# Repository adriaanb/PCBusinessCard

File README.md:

# PCBusinessCard
Another PCB Business Card, this time combining the functionality of an Arduino Leonardo with a capacitive touch interface.

The aim is to provide new contacts some insights into my passions, way of working, and creative style. It also allows me to hand out a tool I use frequently and enable people to discover its potential..

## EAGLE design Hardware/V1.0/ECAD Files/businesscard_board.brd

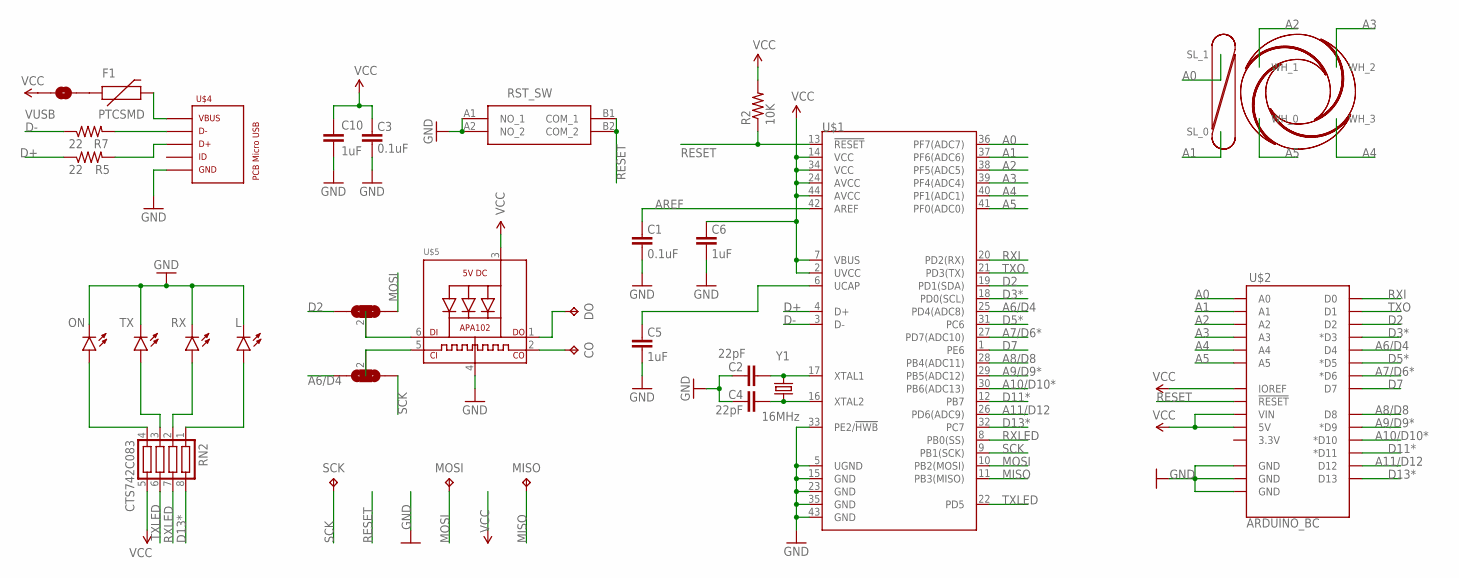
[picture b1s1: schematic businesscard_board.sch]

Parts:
C1, C3: 0.1uF; 0603-CAP
C2, C4: 22pF; 0603-CAP
C5, C6, C10: 1uF; 0603-CAP
CO: TPTP12R; TP12R
D2-/-°-MOSI, D4-/-°-SCK: SOLDER_JP_3WAY
DO: TPTP12R; TP12R
F1: PTCSMD; PTC-1206
L: LED; LED-0603_NOMARKER
MISO: TPTP12R; TP12R
MOSI: TPTP12R; TP12R
ON: LED; LED-0603_NOMARKER
R2: 10K; 0603-RES
R5, R7: 22; 0603-RES
RN2: CTS742C083
RST_SW: EVP-BB0AAB000; EVPBB0AAB000
RX: LED; LED-0603_NOMARKER
SCK: TPTP12R; TP12R
TX: LED; LED-0603_NOMARKER
U$1: 32U4; TQFP44_QRCODE
U$2: ARDUINO_BC; ARDUINO_BC_SINGLEROWS
U$3: TOUCH_SENSORS
U$4: PCB_MICRO_USB_B; USB_TYPE_B_SS_2_NO_DIMENSION
U$5: APA1022020; APA102_2020
VUSB: SOLDER_JP
Y1: 16MHz; CRYSTAL-SMD-5X3

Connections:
A0: U$1.36 (PF7(ADC7)), U$2.A0, U$3.SLIDER_1 (SL_1)
A1: U$1.37 (PF6(ADC6)), U$2.A1, U$3.SLIDER_0 (SL_0)
A2: U$1.38 (PF5(ADC5)), U$2.A2, U$3.WHEEL_1 (WH_1)
A3: U$1.39 (PF4(ADC4)), U$2.A3, U$3.WHEEL_2 (WH_2)
A4: U$1.40 (PF1(ADC1)), U$2.A4, U$3.WHEEL_3 (WH_3)
A5: U$1.41 (PF0(ADC0)), U$2.A5, U$3.WHEEL_0 (WH_0)
A6/D4: D4-/-°-SCK.3 (DIS), U$1.25 (PD4(ADC8)), U$2.D4
A7/D6*: U$1.27 (PD7(ADC10)), U$2.D6 (*D6)
A8/D8: U$1.28 (PB4(ADC11)), U$2.D8
A9/D9*: U$1.29 (PB5(ADC12)), U$2.D9 (*D9)
A10/D10*: U$1.30 (PB6(ADC13)), U$2.D10 (*D10)
A11/D12: U$1.26 (PD6(ADC9)), U$2.D12
APA102_CI: D4-/-°-SCK.2 (MID), U$5.5 (CKI)
APA102_CO: CO.TP, U$5.2 (CKO)
APA102_DO: DO.TP, U$5.1 (DO)
AREF: C1.2, U$1.42 (AREF)
D2: D2-/-°-MOSI.3 (DIS), U$1.19 (PD1(SDA)), U$2.D2
D3*: U$1.18 (PD0(SCL)), U$2.D3 (*D3)
D5*: U$1.31 (PC6), U$2.D5 (*D5)
D7: U$1.1 (PE6), U$2.D7
D11*: U$1.12 (PB7), U$2.D11 (*D11)
D13*: RN2.8, U$1.32 (PC7), U$2.D13
D+: R5.1, U$1.4 (D+)
D-: R7.1, U$1.3 (D-)
GND: C1.1, C2.2, C3.1, C4.2, C5.1, C6.1, C10.2, L.C, ON.C, RST_SW.A1 (NO_1), RST_SW.A2 (NO_2), RX.C, TX.C, U$1.5 (UGND), U$1.15 (GND), U$1.23 (GND), U$1.33 (PE2/!HWB), U$1.35 (GND), U$1.43 (GND), U$2.GND@1 (GND), U$2.GND@2 (GND), U$2.GND@3 (GND), U$4.5, U$5.4 (GND)
MISO: MISO.TP, U$1.11 (PB3(MISO))
MOSI: D2-/-°-MOSI.1 (CON), MOSI.TP, U$1.10 (PB2(MOSI))
unnamed: ON.A, RN2.4
unnamed: RN2.3, TX.A
unnamed: L.A, RN2.1
unnamed: RN2.2, RX.A
unnamed: F1.1, VUSB.2
unnamed: D2-/-°-MOSI.2 (MID), U$5.6 (DI)
unnamed: C4.1, U$1.16 (XTAL2), Y1.1
unnamed: C2.1, U$1.17 (XTAL1), Y1.3 (2)
unnamed: C5.2, U$1.6 (UCAP)
unnamed: R7.2, U$4.2
unnamed: R5.2, U$4.3
RESET: R2.1, RST_SW.B1 (COM_1), RST_SW.B2 (COM_2), U$1.13 (!RESET), U$2.RESET@1 (!RESET!)
RXI: U$1.20 (PD2(RX)), U$2.D0
RXLED: RN2.7, U$1.8 (PB0(SS))
SCK: D4-/-°-SCK.1 (CON), SCK.TP, U$1.9 (PB1(SCK))
TXLED: RN2.6, U$1.22 (PD5)
TXO: U$1.21 (PD3(TX)), U$2.D1
USB_PWR: F1.2, U$4.1
VCC: C3.2, C6.2, C10.1, R2.2, RN2.5, U$1.2 (UVCC), U$1.7 (VBUS), U$1.14 (VCC), U$1.24 (AVCC), U$1.34 (VCC), U$1.44 (AVCC), U$2.5V, U$2.5V@2 (VIN), U$2.IOREF, U$5.3 (VDD), VUSB.1

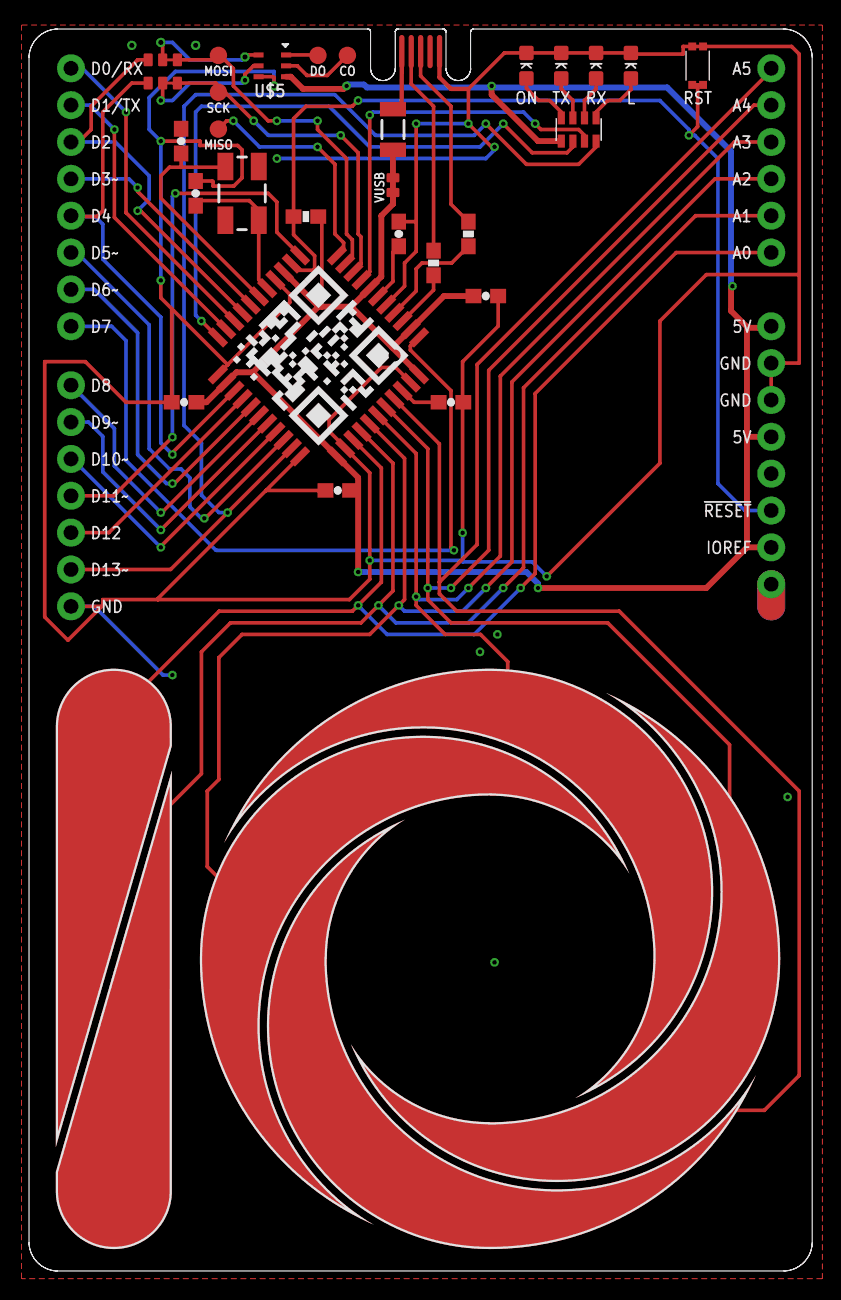
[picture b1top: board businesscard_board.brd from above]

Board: 2 copper layers, 54.0 x 85.6 mm, 31 parts (0 on the bottom side), 46 nets.

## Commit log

2022-09-11 Initial commit
    Initial commit of ECAD files in preparation for next revision
2022-09-21 Fix APA102 pinout
    Fix APA102 pinout, clean up library
